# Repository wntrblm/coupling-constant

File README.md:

# Winterbloom Coupling Constant

Coupling Constant is high-quality, transparent guitar buffer.

More details available at https://winterbloom.com/shop/coupling-constant

## Repository layout

This repository contains the hardware design files and user guide for Coupling Constant:

- **factory/** contains the scripts used to program, test, and calibrate the module after assembly. These scripts are all written in Python.
- **hardware/** contains the hardware design files for the mainboard and blank panel, as well as hardware for automated testing. These are all created using KiCAD.
- **user_guide/** contains the user's guide source files. These are written in Markdown and published using MkDocs.

## License and contributing

Coupling Constant is open-source hardware and software, however, licensing a project like this is a little complicated. Please take a chance to review the [LICENSE](LICENSE.md) file.

We welcome contributions! Please read our [Code of Conduct](CODE_OF_CONDUCT.md) first.

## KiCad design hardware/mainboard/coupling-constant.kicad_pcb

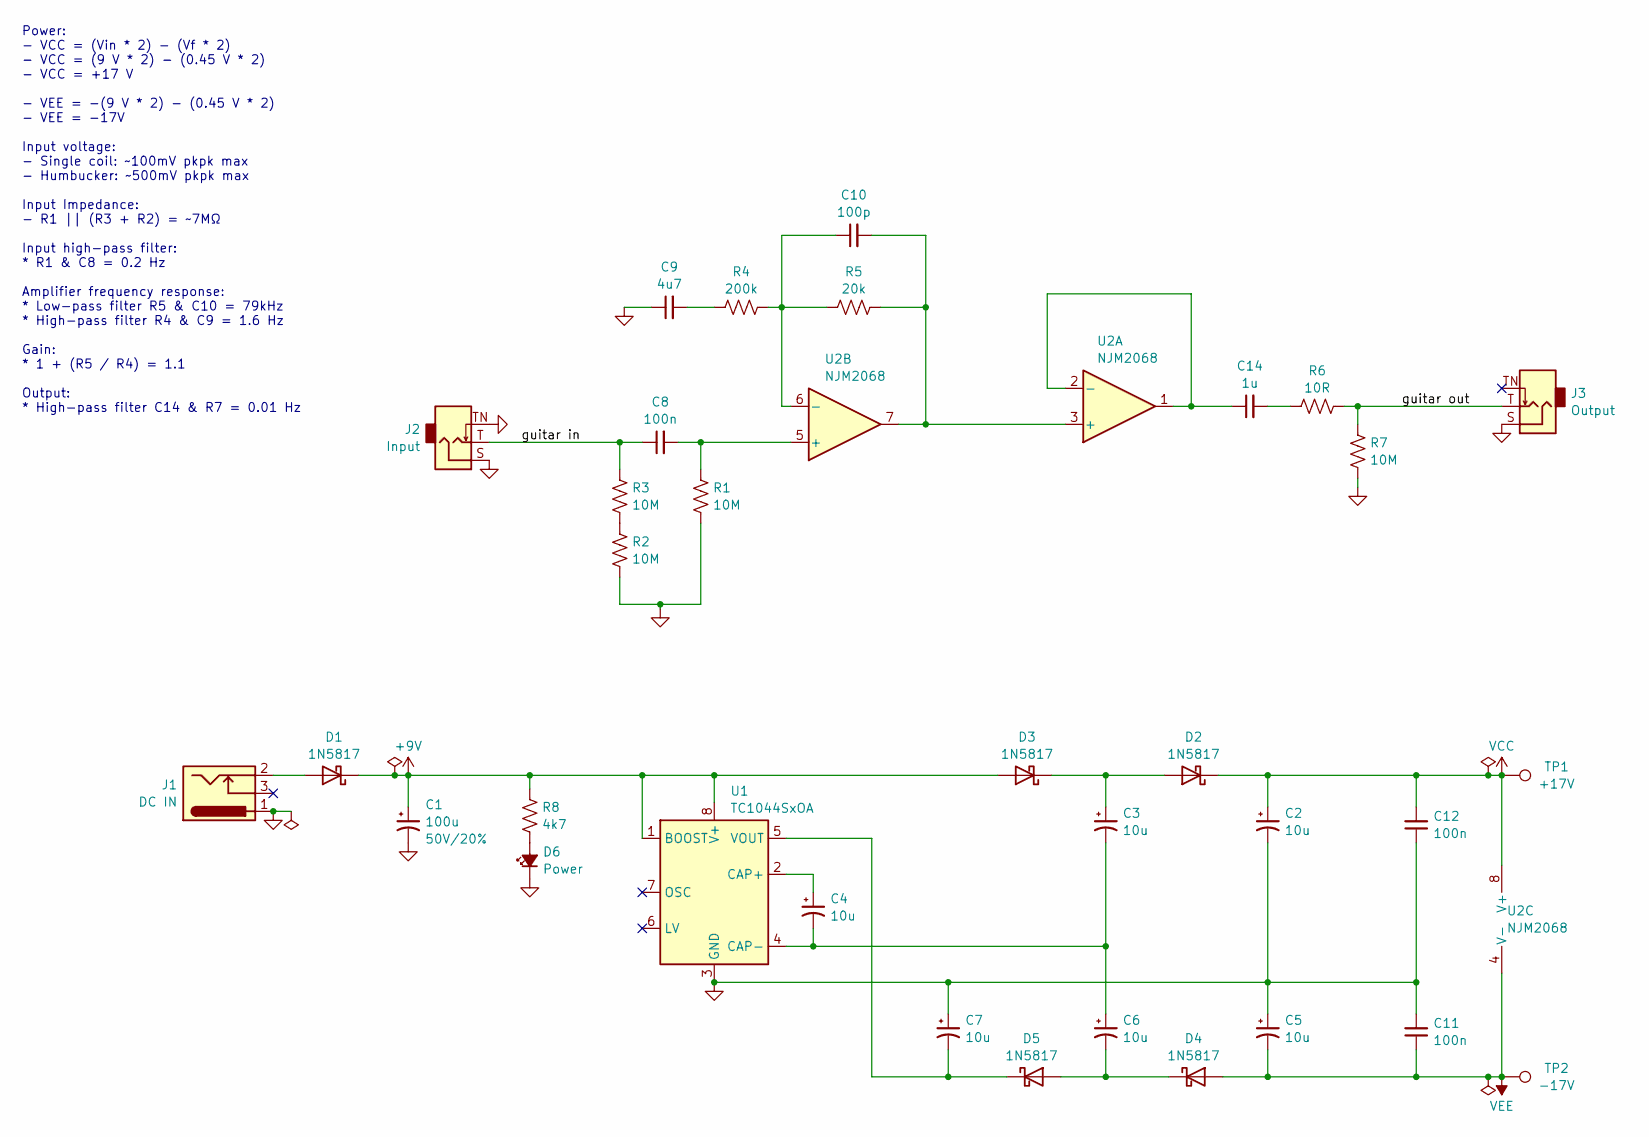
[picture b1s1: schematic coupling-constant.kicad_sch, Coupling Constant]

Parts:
C1: 100u; CP_Elec_8x10.5; Rating 50V/20%; mpn UUD1V101MNL1GS
C2, C3, C4, C5, C6, C7: 10u; C_1206_HandSolder; Rating 25V/10%; mpn GRM21BR61E106KA73L
C8, C11, C12: 100n; C_0805_HandSolder; Rating 50V/10%; mpn CL21B104KBCNNNC
C9: 4u7; C_0805_HandSolder; Rating 25V/10%; mpn CL21A475KAQNNNE
C10: 100p; C_0805_HandSolder; Rating 25V/5%; mpn CC0805JRNPO9BN101
C14: 1u; C_0805_HandSolder; Rating 25V/10%; mpn CL21A105KBCLNNC
D1, D2, D3, D4, D5: 1N5817; D_SOD-123+SOD-123F; Rating 40V; mpn B5819W
D6: Power; LED_D3.0mm
J1: DC IN; BarrelJack_CUI_PJ-102AH_Horizontal; mpn PJ-102A
J2: Input; Jack_6.35mm_Neutrik_NMJ4HCD2_Horizontal
J3: Output; Jack_6.35mm_Neutrik_NMJ4HCD2_Horizontal
R1, R2, R3, R7: 10M; R_0805_HandSolder; Rating 125mW/10%; mpn RC0805JR-0710ML
R4: 200k; R_0805_HandSolder; Rating 125mW/1%/Thin; mpn RT0805DRD07200KL
R5: 20k; R_0805_HandSolder; Rating 125mW/1%/Thin; mpn RT0805FRE0720KL
R6: 10R; R_0805_HandSolder; Rating 125mW/1%/Thin; mpn RT0805FRE0710RL
R8: 4k7; R_0805_HandSolder; Rating 125mW/1%/Thin; mpn RT0805FRE074K7L
TP1: +17V; TestPoint_Pad_D1.0mm
TP2: -17V; TestPoint_Pad_D1.0mm
U1: TC1044SxOA; SOIC-8_3.9x4.9mm_P1.27mm; mpn TC1044SEOA713
U2: NJM2068; SOIC-8+DMP-8_5mmx5mm_P1.27mm; mpn NJM2068M

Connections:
+9V: C1.1, D1.1 (K), D3.2 (A), R8.2, U1.1 (BOOST), U1.8 (V+)
/guitar in: C8.1, J2.T, R3.1
/guitar out: J3.T, R6.1, R7.2
GND: C1.2, C2.2, C5.1, C7.1, C9.1, C11.2, C12.1, D6.1 (K), J1.1, J2.S, J2.TN, J3.S, R1.2, R2.2, R7.1, U1.3 (GND)
unnamed: C9.2, R4.1
unnamed: C14.2, R6.2
unnamed: D1.2 (A), J1.2
unnamed: C3.1, D2.2 (A), D3.1 (K)
unnamed: C6.2, D4.1 (K), D5.2 (A)
unnamed: C7.2, D5.1 (K), U1.5 (VOUT)
unnamed: D6.2 (A), R8.1
unnamed: R2.1, R3.2
unnamed: C4.1, U1.2 (CAP+)
unnamed: C3.2, C4.2, C6.1, U1.4 (CAP-)
unnamed: C10.2, R5.2, U2.3 (+), U2.7
unnamed: C14.1, U2.1, U2.2 (-)
unnamed: C8.2, R1.1, U2.5 (+)
unnamed: C10.1, R4.2, R5.1, U2.6 (-)
VCC: C2.1, C12.2, D2.1 (K), TP1.1, U2.8 (V+)
VEE: C5.2, C11.1, D4.2 (A), TP2.1, U2.4 (V-)

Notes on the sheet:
Power: - VCC = (Vin * 2) - (Vf * 2) - VCC = (9 V * 2) - (0.45 V * 2) - VCC = +17 V - VEE = -(9 V * 2) - (0.45 V * 2) - VEE = -17V Input voltage: - Single coil: ~100mV pkpk max - Humbucker: ~500mV pkpk max Input Impedance: - R1 || (R3 + R2) = ~7MΩ Input high-pass filter: * R1 & C8 = 0.2 Hz Amplifier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

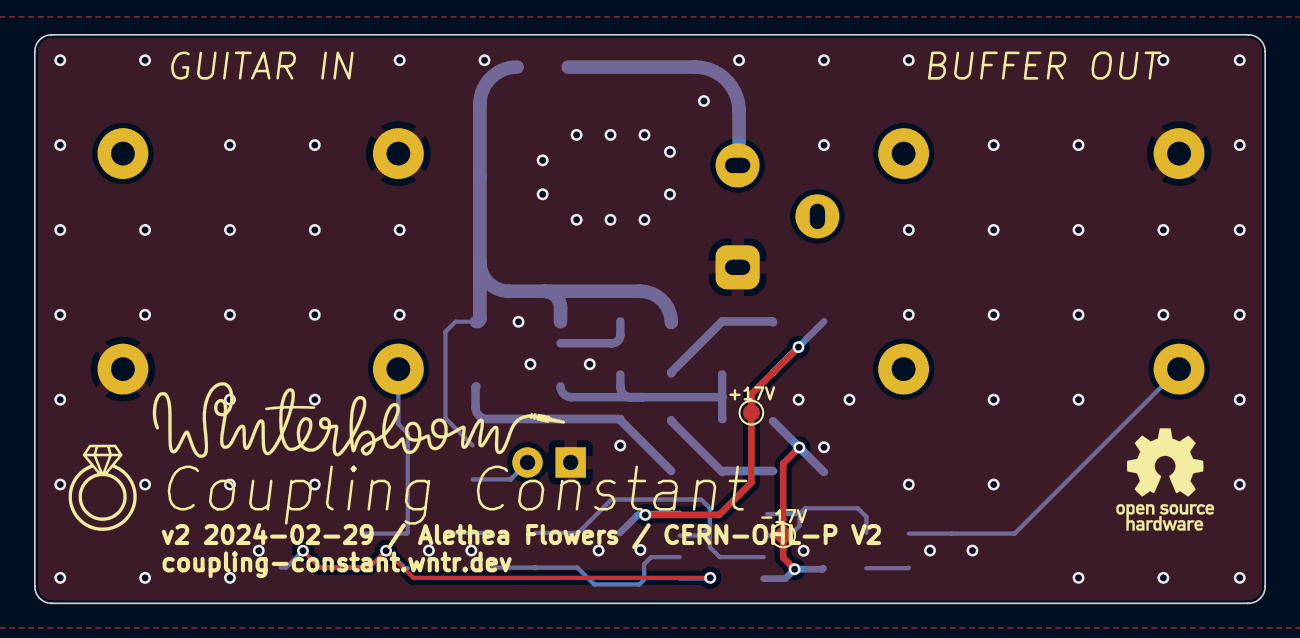
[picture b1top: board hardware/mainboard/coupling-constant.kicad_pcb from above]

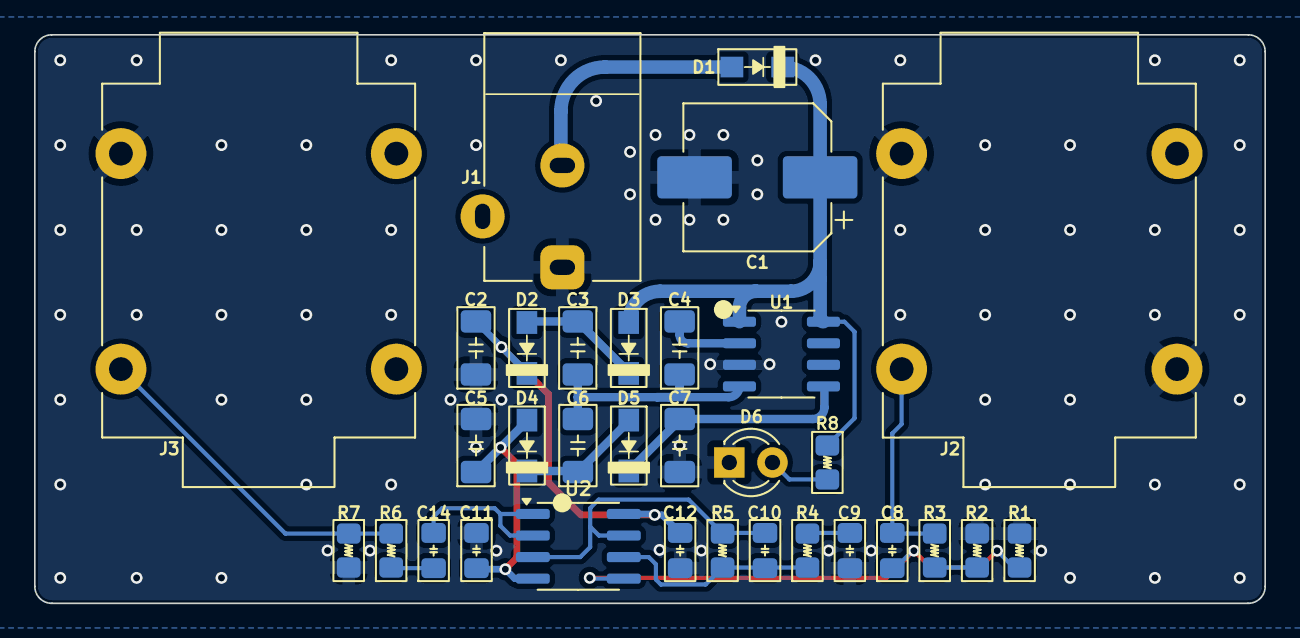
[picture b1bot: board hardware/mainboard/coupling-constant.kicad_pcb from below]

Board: 2 copper layers, 72.5 x 33.5 mm, 34 parts (32 on the bottom side), 20 nets.

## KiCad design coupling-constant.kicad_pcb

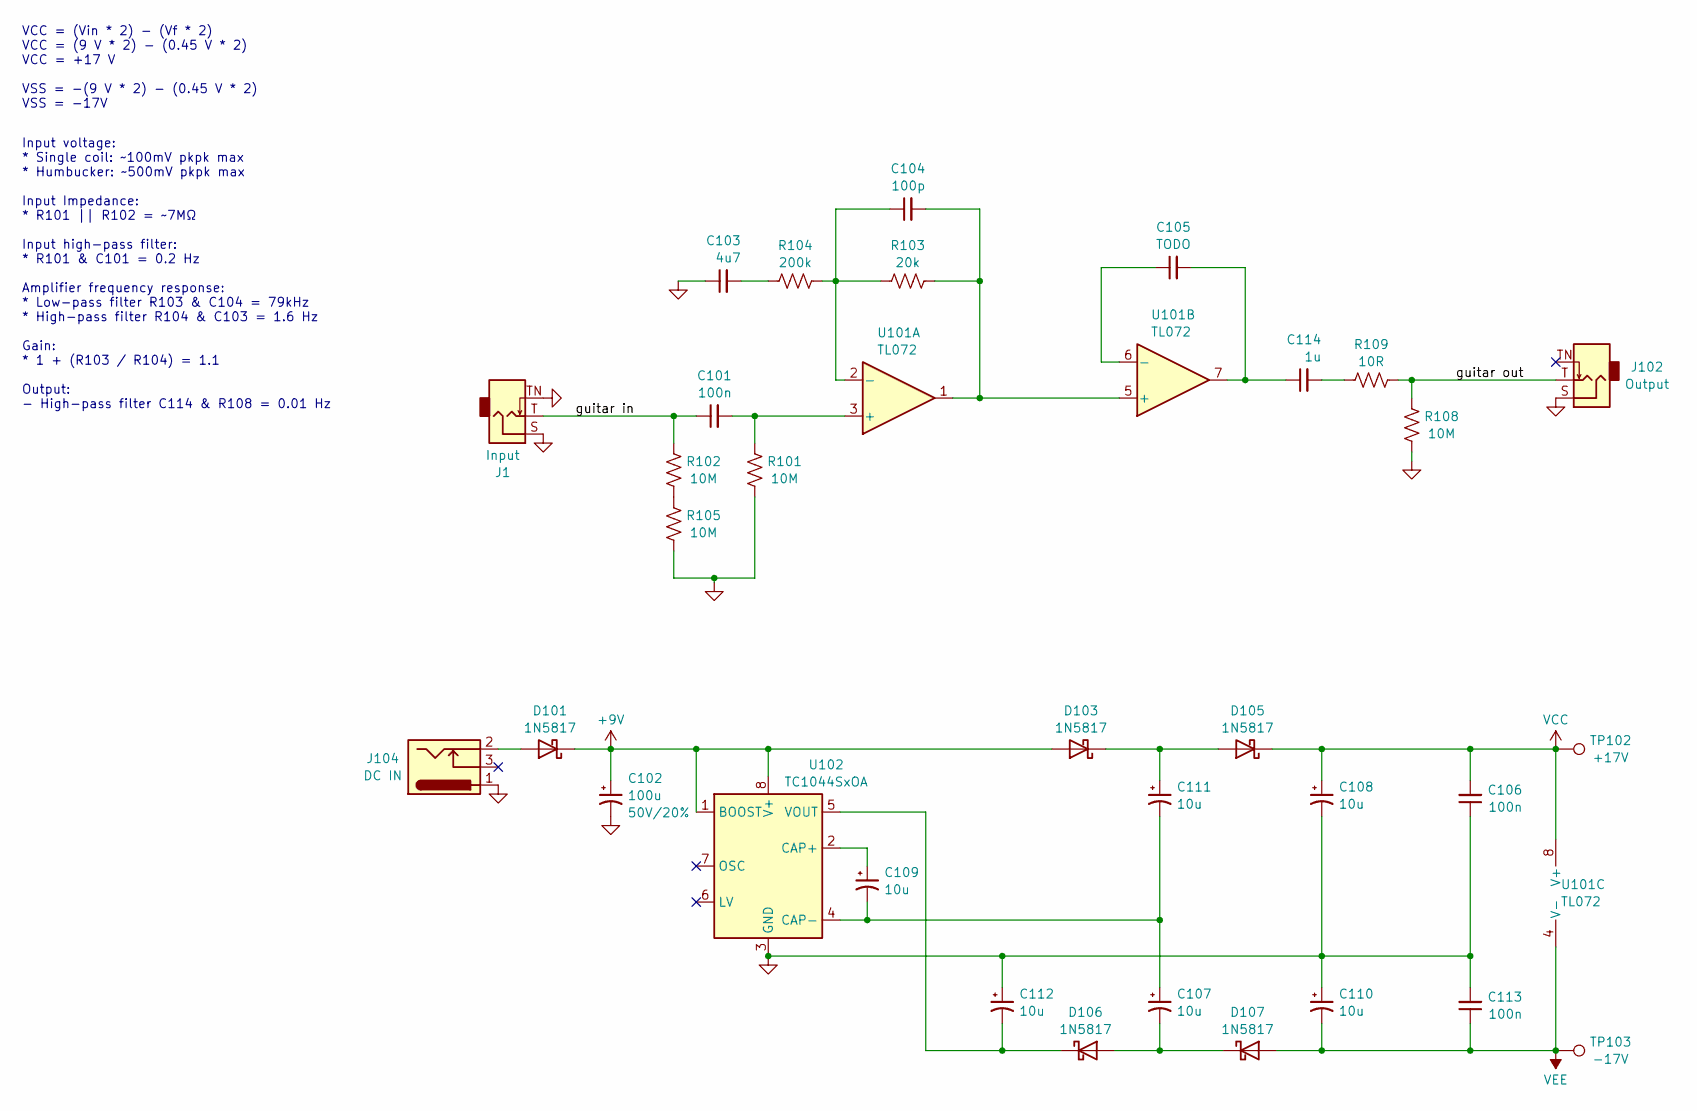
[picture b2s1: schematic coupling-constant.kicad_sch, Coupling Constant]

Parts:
C101, C106, C113: 100n; C_0805_HandSolder; Rating 50V/10%; mpn CL21B104KBCNNNC
C102: 100u; CP_Elec_8x10.5; Rating 50V/20%; mpn UUD1V101MNL1GS
C103: 4u7; R_0805_HandSolder; Rating 25V/10%; mpn CL21A475KAQNNNE
C104: 100p; R_0805_HandSolder; Rating 25V/5%; mpn CC0805JRNPO9BN101
C105: TODO; R_0805_HandSolder; Rating 25V/10%
C107, C108, C109, C110, C111, C112: 10u; C_1206_HandSolder; Rating 25V/10%; mpn GRM21BR61E106KA73L
C114: 1u; C_0805_HandSolder; Rating 25V/10%; mpn CL21A105KBCLNNC
D101, D103, D105, D106, D107: 1N5817; D_SOD-123+SOD-123F; Rating 40V; mpn B5819W
J1: Input; Jack_6.35mm_Neutrik_NMJ4HCD2_Horizontal
J102: Output; Jack_6.35mm_Neutrik_NMJ4HCD2_Horizontal
J104: DC IN; BarrelJack_CUI_PJ-102AH_Horizontal; mpn PJ-102A
R101, R102, R105, R108: 10M; R_0805_HandSolder; Rating 125mW/10%; mpn RC0805JR-0710ML
R103: 20k; R_0805_HandSolder; Rating 125mW/1%/Thin; mpn RT0805FRE0720KL
R104: 200k; R_0805_HandSolder; Rating 125mW/1%/Thin; mpn RT0805DRD07200KL
R109: 10R; C_0805_HandSolder; Rating 125mW/1%/Thin; mpn RT0805FRE0710RL
TP102: +17V; TestPoint_Pad_D1.0mm
TP103: -17V; TestPoint_Pad_D1.0mm
U101: TL072; TSSOP-8_4.4x3mm_P0.65mm; mpn TL072CPWR
U102: TC1044SxOA; SOIC-8_3.9x4.9mm_P1.27mm; mpn TC1044SEOA713

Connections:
+9V: C102.1, D101.1 (K), D103.2 (A), U102.1 (BOOST), U102.8 (V+)
/guitar in: C101.1, J1.T, R102.1
/guitar out: J102.T, R108.2, R109.1
GND: C102.2, C103.1, C106.1, C108.2, C110.1, C112.1, C113.2, J1.S, J1.TN, J102.S, J104.1, R101.2, R105.2, R108.1, U102.3 (GND)
unnamed: C103.2, R104.1
unnamed: C105.2, C114.1, U101.7
unnamed: C114.2, R109.2
unnamed: D101.2 (A), J104.2
unnamed: C111.1, D103.1 (K), D105.2 (A)
unnamed: C107.2, D106.2 (A), D107.1 (K)
unnamed: C112.2, D106.1 (K), U102.5 (VOUT)
unnamed: R102.2, R105.1
unnamed: C101.2, R101.1, U101.3 (+)
unnamed: C104.1, R103.1, R104.2, U101.2 (-)
unnamed: C104.2, R103.2, U101.1, U101.5 (+)
unnamed: C105.1, U101.6 (-)
unnamed: C109.1, U102.2 (CAP+)
unnamed: C107.1, C109.2, C111.2, U102.4 (CAP-)
VCC: C106.2, C108.1, D105.1 (K), TP102.1, U101.8 (V+)
VEE: C110.2, C113.1, D107.2 (A), TP103.1, U101.4 (V-)

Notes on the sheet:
Input voltage: * Single coil: ~100mV pkpk max * Humbucker: ~500mV pkpk max Input Impedance: * R101 || R102 = ~7MΩ Input high-pass filter: * R101 & C101 = 0.2 Hz Amplifier frequency response: * Low-pass filter R103 & C104 = 79kHz * High-pass filter R104 & C103 = 1.6 Hz Gain: * 1 + (R103 / R104) = 1.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
VCC = (Vin * 2) - (Vf * 2) VCC = (9 V * 2) - (0.45 V * 2) VCC = +17 V VSS = -(9 V * 2) - (0.45 V * 2) VSS = -17V

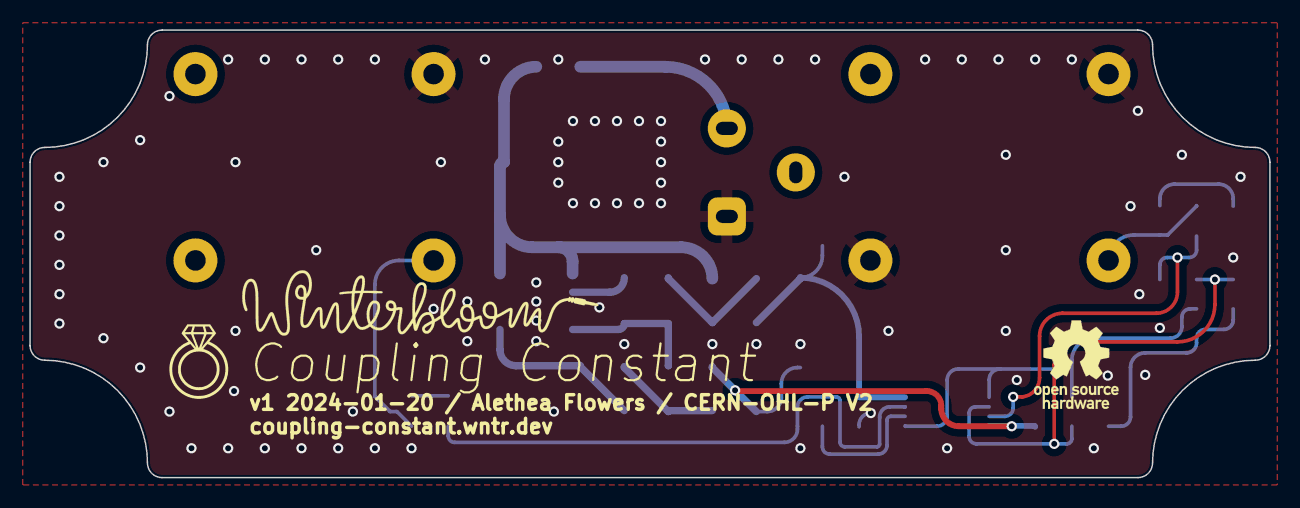
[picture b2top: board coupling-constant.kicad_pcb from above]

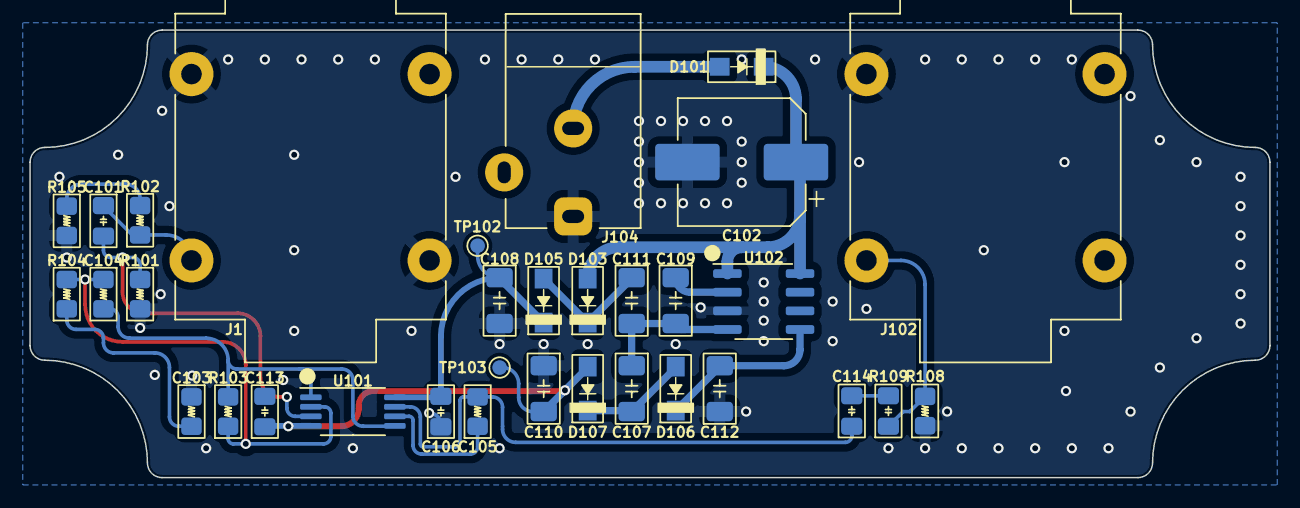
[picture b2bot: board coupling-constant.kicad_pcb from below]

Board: 2 copper layers, 84.5 x 30.5 mm, 33 parts (33 on the bottom side), 20 nets.

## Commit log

2024-01-11 add .gitignore
2024-01-11 initial version
2024-01-21 v1, fixup op amp inputs
2024-02-13 finalize v1
2024-02-16 project structure
2024-02-16 fix drawing sheet path
2024-02-23 hardware: fix mpn for resistor
2024-02-29 hardware: revision 2
    - Swap TL072 for NJM2068
    - Swap footprint for one compatible with SOIC-8 and DMP-8, making it easier to swap op-amps
    - Remove feedback cap in output amplifier, it's not needed and has only caused problems.
    - Update everything to KiCAD 8

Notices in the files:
coupling-constant.kicad_pcb:
CERN-OHL-P V2
